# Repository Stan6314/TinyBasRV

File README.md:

Microcomputer TinyBasRV
======================

The TinyBasRV microcomputer is a very simple device that even an electrical engineering beginner should be able to assemble and put into operation. It resembles simple 8-bit computers from the 1980s. After assembly, it can be programmed very easily using the Tiny BASIC language, which should be manageable even for those who have never programmed before. The basis is a small 32-bit RISC-V processor cooperating with serial I2C memory, where the user-created program is stored.

A microcomputer is suitable for the first introduction to computing technology when teaching hardware and software. It can be used not only for educational purposes, but can also be used as a control element for simple electronic devices.

Technical data for TinyBasRV
----------------------------

*   TinyBasHW_KiCad - HW documents (schematic and printed circuit board) in KiCad 9.0 format
*   src - Source files for TinyBasRV for CH32V003 created in MounRiver 2.10 environment
*   Bin - Compiled binary content in HEX format for direct loading into CH32V003 memory
*   Manuals - Manuals for HW, Tiny BASIC programming language and its examples and advice for beginners
*   EEPROM_examples - Contents of serial EEPROM memory in HEX format with examples of 8 ready-made Tiny BASIC sample programs for loading into microcomputer memory

Requirements for building and operating a TinyBasRV
---------------------------------------------------

*   Printed circuit board
*   Electrical components according to the list in the TinyBasHW manual
*   WCHLinkE programmer for programming CH32V003
*   Monitor with VGA input
*   Keyboard with PS2 connector
*   5V power supply

Using a microcomputer
---------------------

The assembled microcomputer only requires a 5 V power supply and a VGA monitor and PS2 keyboard connection. It is possible to use both a modern monitor and keyboard...

... so you can also create an old "retro" computer (if you can still find historical computer parts).

After debugging the program, the TinyBasRV microcomputer can work independently without a monitor and keyboard and control, for example, some LED lighting effects.

* * *

Mikropočítač TinyBasRV
======================

Mikropočítač TinyBasRV je velmi jednoduché zařízení, které by měl dokázat sestavit a uvést do provozu i elektrotechnický začátečník. Podobá se jednoduchým 8bitovým počítačům z 80tých let. Po sestavení jej lze velmi jednoduše programovat pomocí jazyka Tiny BASIC, který by měl zvládnout i ten, kdo dříve neprogramoval. Základem je malý 32bitový RISC-V procesor spolupracující se sériovou I2C pamětí, kam se ukládá uživatelem tvořený program.

Mikropočítač je vhodný pro první seznámení s výpočetní technikou při výuce technického i programového vybavení. Může být použit nejen pro výukové účely, ale lze jej nasadit jako řídicí prvek pro jednoduché elektronické přístroje.

Technické podklady pro TinyBasRV
--------------------------------

*   TinyBasHW_KiCad - HW podklady (schéma a plošný spoj) ve formátu programu KiCad 9.0
*   src - Zdrojové soubory k TinyBasRV pro CH32V003 vytvořené v prostředí MounRiver 2.10
*   Bin - Přeložený binární obsah ve formátu HEX pro přímé nahrání do paměti CH32V003
*   Manuals - Manuály pro HW, programovací jazyk Tiny BASIC a jeho příklady a rady pro začátečníky
*   EEPROM_examples - Obsah sériové EEPROM paměti ve formátu HEX s příklady 8 hotových ukázkových programů Tiny BASIC pro nahrání do paměti mikropočítače

Požadavky pro stavbu a provoz TinyBasRV
---------------------------------------

*   Deska plošného spoje
*   Elektrotechnické součástky podle seznamu v manuálu TinyBasHW
*   Programátor WCHLinkE pro naprogramování CH32V003
*   Monitor s VGA vstupem
*   Klávesnice s konektorem PS2
*   Napájecí zdroj 5 V

Použití mikropočítače
---------------------

Sestavený mikropočítač vyžaduje pouze napájecí zdroj 5 V a připojení VGA monitoru a PS2 klávesnice. Je možné použít jak moderní monitor a klávesnici...

... tak si vytvořit i starý "retro" počítač (pokud ještě najdete dnes již historické počítačové díly).

Po odladění programu, může mikropočítač TinyBasRV pracovat samostatně bez monitoru a klávesnice a řídit např. nějaké světelné LED efekty.

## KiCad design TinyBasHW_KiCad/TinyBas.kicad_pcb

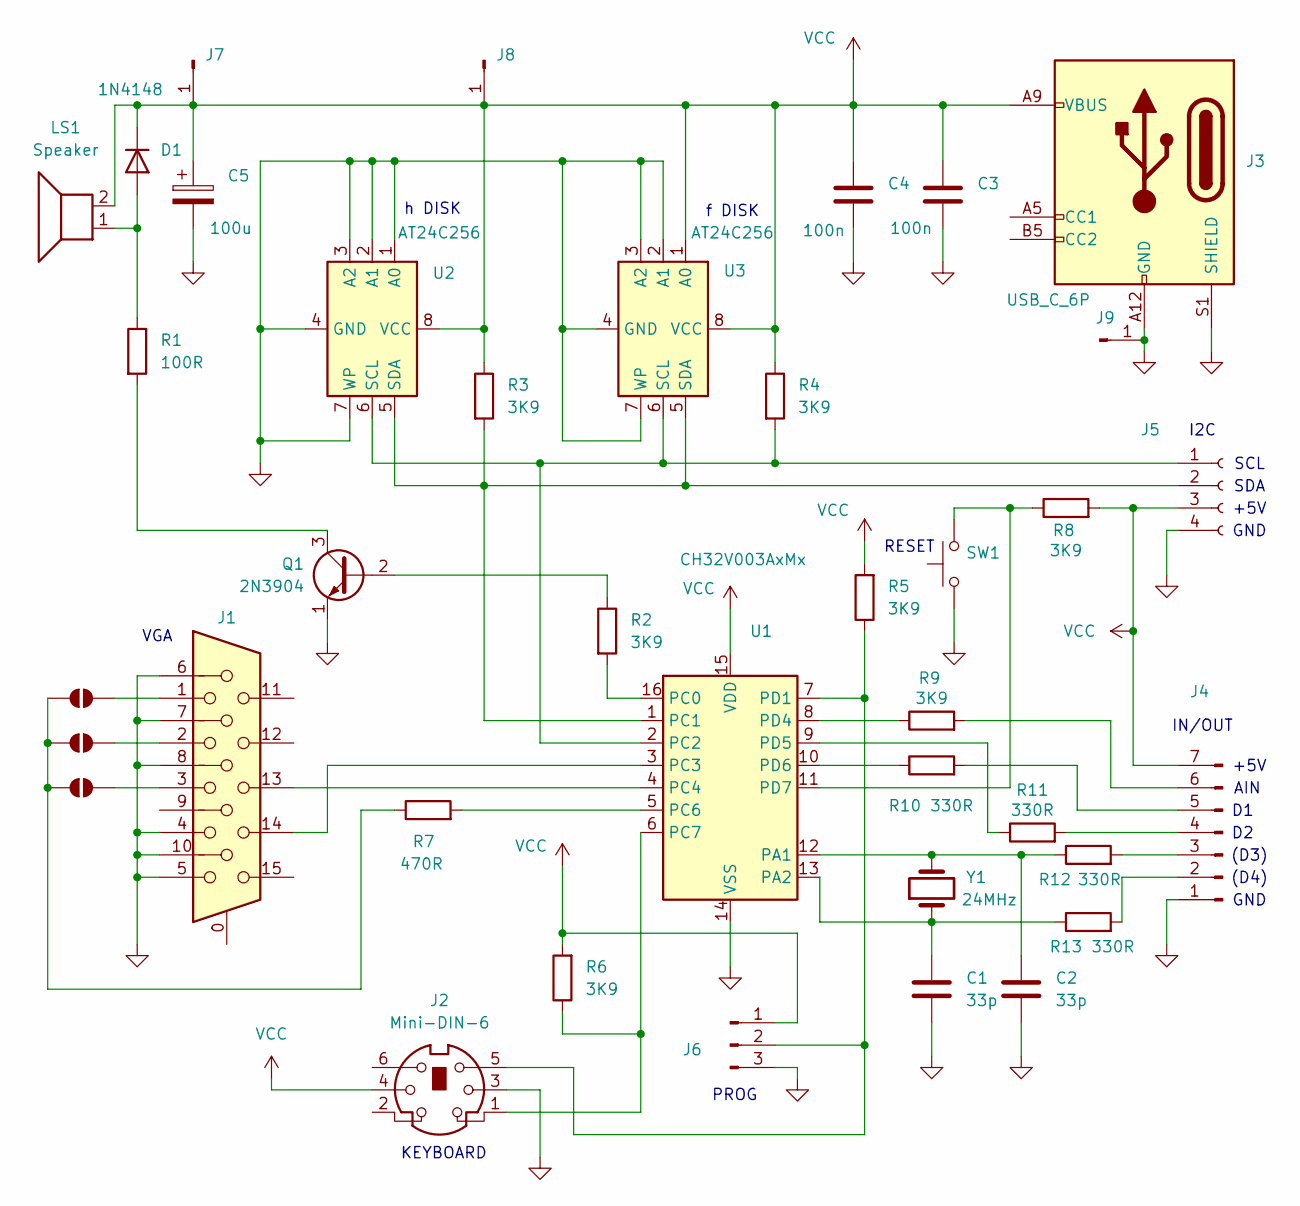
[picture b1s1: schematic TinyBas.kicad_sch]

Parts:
C1, C2: 33p; C_Disc_D6.0mm_W2.5mm_P5.00mm
C3, C4: 100n; C_Disc_D6.0mm_W2.5mm_P5.00mm
C5: 100u; CP_Radial_D7.5mm_P2.50mm
D1: 1N4148; D_DO-35_SOD27_P7.62mm_Horizontal
J1: DE15_Socket_HighDensity_MountingHoles; DSUB-15-HD_Socket_Horizontal_P2.29x2.54mm_EdgePinOffset8.35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
J2: Mini-DIN-6; Connector_Mini-DIN_Female_6Pin_2rows
J3: USB_C_6P; USB_C_Receptacle_GCT_USB4125-xx-x_6P_TopMnt_Horizontal
J4: Conn_01x07_Pin; PinHeader_1x07_P2.54mm_Vertical
J5: Conn_01x04_Socket; PinSocket_1x04_P2.54mm_Horizontal
J6: Conn_01x03_Pin; PinHeader_1x03_P2.54mm_Vertical
J7, J8, J9: Conn_01x01_Pin; PinHeader_1x01_P2.54mm_Vertical
JP5, JP6, JP7: SolderJumper_2_Open; R_0805_2012Metric_Pad1.20x1.40mm_HandSolder
LS1: Speaker; Indicator_PUI_AI-1440-TWT-24V-2-R
Q1: 2N3904; TO-92_Inline_Wide
R1: 100R; R_Axial_DIN0207_L6.3mm_D2.5mm_P7.62mm_Horizontal
R2, R3, R4, R5, R6, R8, R9: 3K9; R_Axial_DIN0207_L6.3mm_D2.5mm_P7.62mm_Horizontal
R7: 470R; R_Axial_DIN0207_L6.3mm_D2.5mm_P7.62mm_Horizontal
R10, R11, R12, R13: 330R; R_Axial_DIN0207_L6.3mm_D2.5mm_P7.62mm_Horizontal
SW1: SW_Push; SW_Tactile_SKHH_Angled
U1: CH32V003AxMx; SOP-16_3.9x9.9mm_P1.27mm
U2: AT24C256; SOIC-8_3.9x4.9mm_P1.27mm
U3: AT24C256; DIP-8_W7.62mm_LongPads
Y1: 24MHz; Crystal_HC49-U_Vertical

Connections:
GND: C1.2, C2.2, C3.2, C4.2, C5.2, J1.4, J1.5, J1.6, J1.7, J1.8, J1.10, J2.3, J3.A12 (GND), J3.B12 (GND), J3.S1 (SHIELD), J4.1, J5.4, J6.3, J9.1, Q1.1 (E), SW1.1, U1.14 (VSS), U2.1 (A0), U2.2 (A1), U2.3 (A2), U2.4 (GND), U2.7 (WP), U3.2 (A1), U3.3 (A2), U3.4 (GND), U3.7 (WP)
unnamed: D1.2 (A), LS1.1, R1.1
unnamed: J4.2, R13.2
unnamed: J4.3, R12.2
unnamed: J4.4, R11.2
unnamed: J4.5, R10.2
unnamed: J4.6, R9.2
unnamed: J5.1, R4.2, U1.2 (PC2), U2.6 (SCL), U3.6 (SCL)
unnamed: J5.2, R3.2, U1.1 (PC1), U2.5 (SDA), U3.5 (SDA)
unnamed: J2.5, J6.2, R5.1, U1.7 (PD1)
unnamed: JP5.1 (A), JP6.1 (A), JP7.1 (A), R7.1
unnamed: J1.2, JP5.2 (B)
unnamed: J1.3, JP6.2 (B)
unnamed: J1.1, JP7.2 (B)
unnamed: Q1.2 (B), R2.1
unnamed: Q1.3 (C), R1.2
unnamed: C2.1, R12.1, U1.12 (PA1), Y1.2
unnamed: C1.1, R13.1, U1.13 (PA2), Y1.1
unnamed: R2.2, U1.16 (PC0)
unnamed: J1.14, U1.3 (PC3)
unnamed: J1.13, U1.4 (PC4)
unnamed: R7.2, U1.5 (PC6)
unnamed: J2.1, R6.1, U1.6 (PC7)
unnamed: R9.1, U1.8 (PD4)
unnamed: R11.1, U1.9 (PD5)
unnamed: R10.1, U1.10 (PD6)
unnamed: R8.1, SW1.2, U1.11 (PD7)
VCC: C3.1, C4.1, C5.1, D1.1 (K), J2.4, J3.A9 (VBUS), J3.B9 (VBUS), J4.7, J5.3, J6.1, J7.1, J8.1, LS1.2, R3.1, R4.1, R5.2, R6.2, R8.2, U1.15 (VDD), U2.8 (VCC), U3.1 (A0), U3.8 (VCC)

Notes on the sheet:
f DISK
KEYBOARD
h DISK
PROG
RESET
SCL
+5V
(D4)
GND
(D3)
AIN
VGA
IN/OUT
SDA
I2C

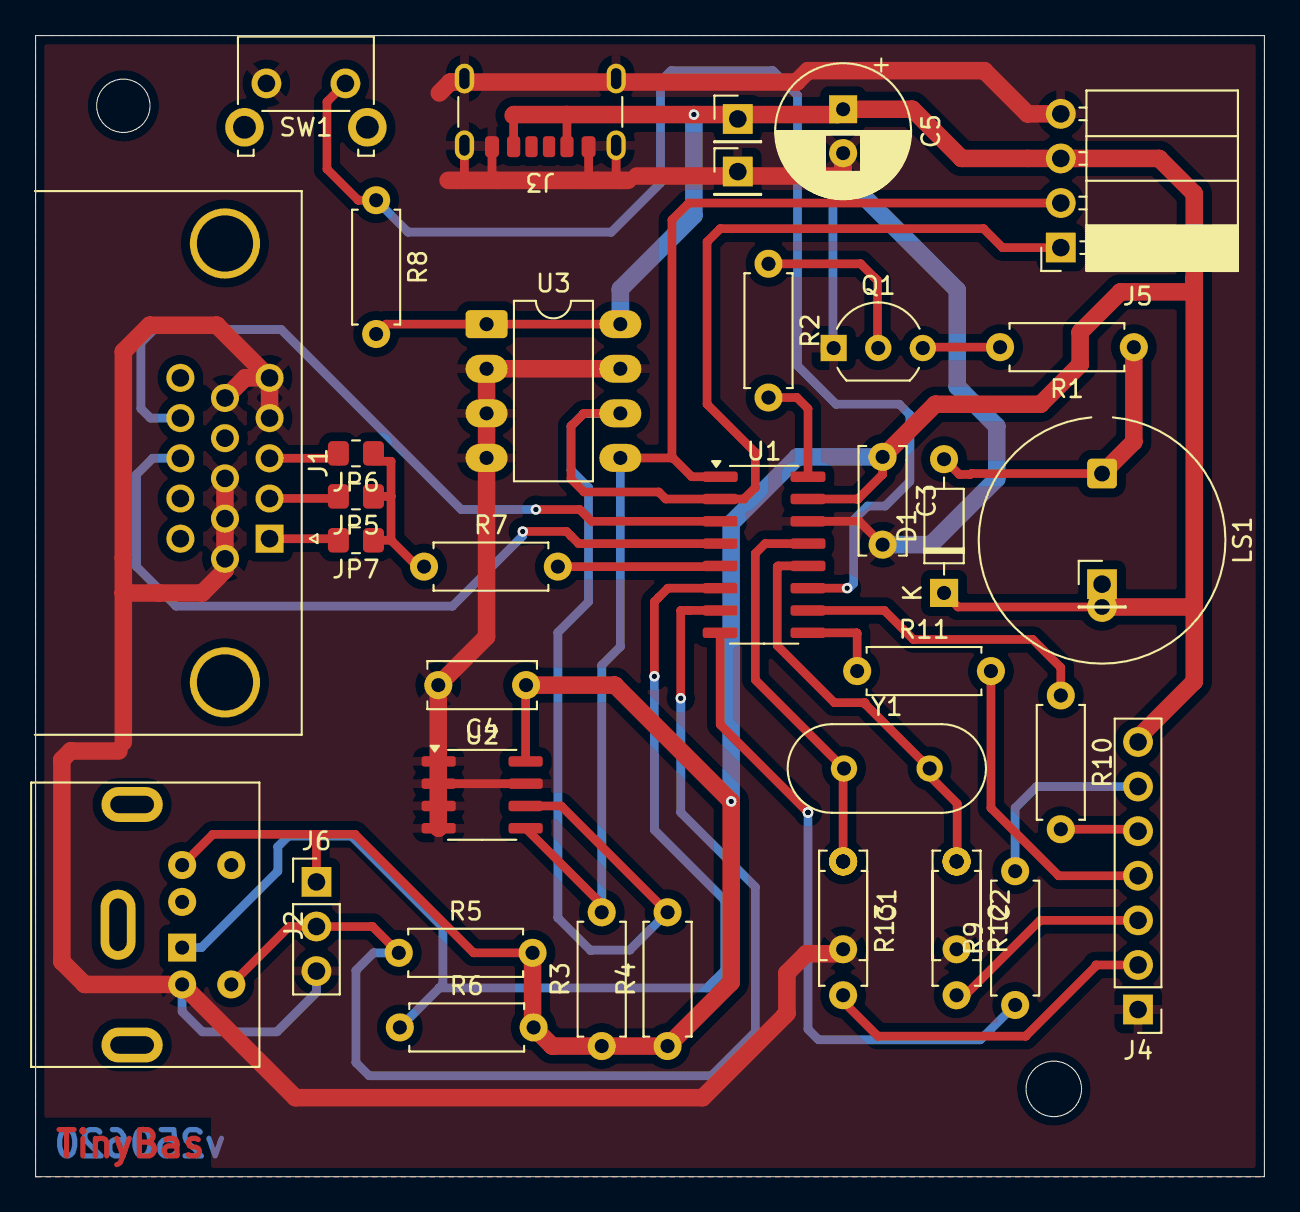
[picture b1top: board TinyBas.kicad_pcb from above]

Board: 2 copper layers, 70.0 x 65.0 mm, 38 parts (0 on the bottom side), 28 nets.

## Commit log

2025-08-19 Correction of minor typos
    Fix minor errors in the English manual
2025-11-05 Adding completed tasks
2025-11-07 Correction of example 32
2025-11-26 Clarification of the RUN command
2026-01-02 Fixed example 31
2026-01-25 Problem with WCH-LinkUtility
2026-01-27 HEX file download solved
2026-01-28 Moved HEX to ZIP file
2026-03-08 Speed up TIM1_UP_IRQHandler
